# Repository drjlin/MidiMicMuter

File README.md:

# Midi Microphone Muter

This repository provides code and hardware for a little tool in the form of a Y-adapter to be used on stage to mute a single microphone by receiving a MIDI control change signal.

## Motivation

For me as a drummer doing some additional background vocals in my band, there is always the problem of cymbal bleed on the vocal microphone signal. So while I was not singing, our live mixing engineer used to turn down the volume of my microphone signal at the risk of not having it back when needed again. Since a MIDI track was already running synchronized with our show for controlling lights and guitar effects, our mixing engineer Jakob had the idea to also use the MIDI signal to mute the microphone in those parts of the songs where it is not needed. However, all available solutions were not at all compact and satisfying, so I decided to build my own device.

## How it works

The electronics pcb is designed to fit into an XLR cable connector. This way the full device is nothing more than a Y-shaped cable with two connectors on the input side (Mic and MIDI In) and one XLR connector on the output side to deliver the occasionally muted signal to the microphone preamp.

Inspired by another blog post (https://mitxela.com/projects/midi_on_the_attiny), I decided to use the 5V power line from MIDI to power an ATtiny85 which decodes the serial MIDI data and pulls outputs high for an LED and an analog switch to turn the audio off.

Contrary to the popular advice, no optocoupler was used on the receiving unit to save space and allow to directly use MIDI as a voltage source. Pros and cons of this approach are described in detail in the link above.

Another variant of the device having the electronics mounted into a separate small box is currently in the planning phase. This would allow for proper MIDI decoupling, provide an additional MIDI Out connector and XLR connectors to make it more modular and independent of the needed cable lengths. On the downside, this would take a little more space and require another voltage source (battery, 5V connector or using microphone phantom power).

## Hardware

PCB dimensions are 23.15x9.70 mm and therefore it fits nicely into a standard XLR connector. On the input side, there are pin header terminals for MIDI In (GND, +5V, Signal) and Mic In (analog GND, Signal +, Signal -). On the output side, there is an additional Mic Out 3-pin terminal. The ATtiny85 is a cheap microcontroller which can be run without any peripherals at low power, which makes it the perfect choice for processing the program logic. TS5A22364 from Texas Instruments is a 2-channel analog switch with negative signaling capability, perfectly suited for audio switching. It takes audio Signal + and Signal - on its normally closed inputs and is connected to Mic Out on its common output pins. The only additional elements on the PCB are a 33 uF capacitor for smoothing the input voltage, a pull-up resistor and a small stabilizing 1nF capacitor on the MIDI signal line, a pull-down resistor on the output line of the ATtiny85 connecting to the analog switch and an optional LED with serial resistor to visualize when the device is in mute mode (mainly for testing).

Because audio signals are connected to the normally closed pins of the analog switch, the default behavior is to let the audio flow from input to output and only mute it on respective incoming MIDI commands. But keep in mind there is no real bypass, so MIDI has to be connected (and powered) to let audio go through.

Analog (audio) GND is not connected to the digital GND by default. During tests, it was found that the two should be connected to avoid noise on the audio output, but this can easily be achieved by adding an additional cable between the respective pins.

You need to install KiCad (https://www.kicad.org) to be able to open the schematics / pcb / gerber files.

## Software

On the software side, I used a slightly modified version of Nick Gammon's MIDI decoder for ATtiny85 (https://arduino.stackexchange.com/questions/14054/interfacing-an-attiny85-with-midi-via-software-serial?answertab=active#tab-top). I just added the output switching logic when a control change command is received on the specified MIDI channel and CC number (by default: CC 63 on MIDI channel 7).

For programming the ATtiny85, Arduino IDE was used in combination with an Arduino nano as programmer. The procedure is described elsewhere in detail. I followed the description in this link: https://wolles-elektronikkiste.de/en/programming-attiny-with-arduino-code

You need to install Arduino IDE (https://www.arduino.cc/en/software) to be able use the included software.

## Usage

Connect microphone, MIDI in and microphone preamp. By default, the signal will be hearable. Sending CC 63 on MIDI channel 7 with a value between than 64 and 127 will mute the microphone and light up the LED. Another event with a value between 0 and 63 will unmute the line again.

## How to get it

Currently, I'm not planning to sell ready-to-use hardware. But I have some PCBs over that I don't need, so feel free to contact me if interested. Otherwise, everyone is invited to build the device on her / his own. Everything you need should be in the repository. If you have problems or questions, do not hesitate to ask.

## Feedback

Any feedback is appreciated, either on making the device more robust while maintaining the small footprint, or if there are any tips on implementing the in-a-box design. Also, please report any bugs in case you find some.

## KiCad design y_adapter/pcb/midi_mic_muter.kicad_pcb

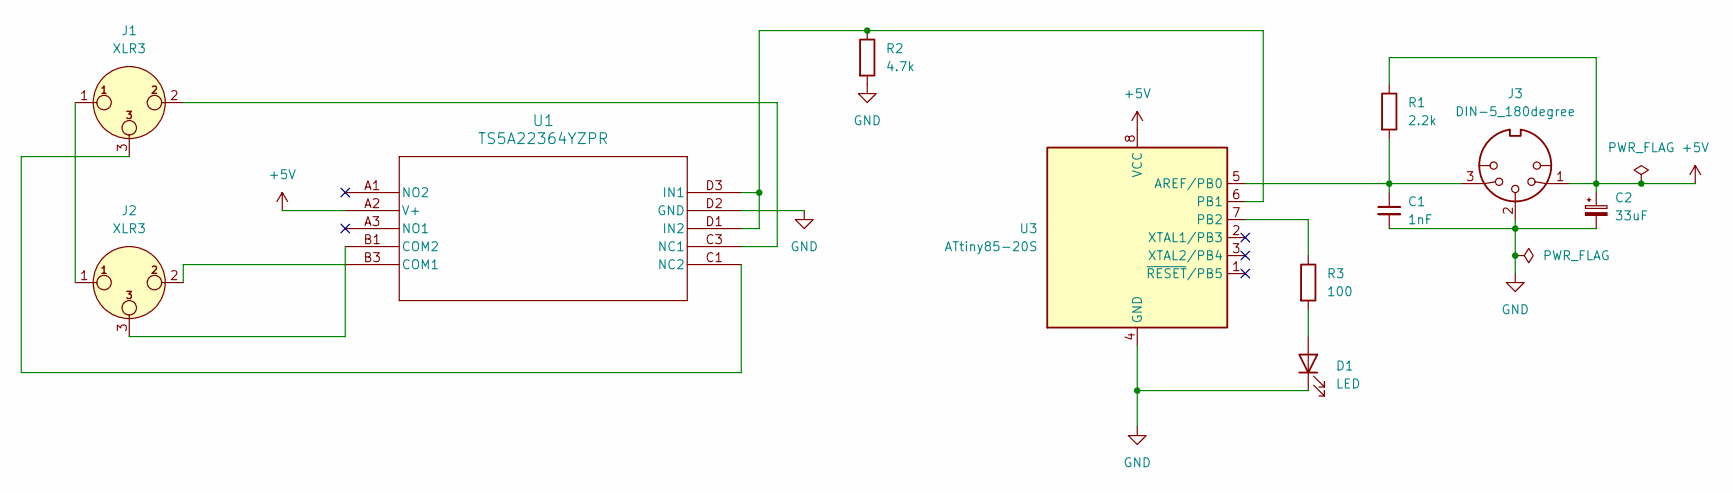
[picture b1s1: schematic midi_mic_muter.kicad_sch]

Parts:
C1: 1nF; C_0603_1608Metric
C2: 33uF; C_0805_2012Metric
D1: LED; LED_0603_1608Metric
J1, J2: XLR3; PinHeader_1x03_P2.54mm_Vertical
J3: DIN-5_180degree; PinHeader_1x03_P2.54mm_Vertical
R1: 2.2k; R_0603_1608Metric
R2: 4.7k; R_0603_1608Metric
R3: 100; R_0603_1608Metric
U1: TS5A22364YZPR; Texas_DSBGA-10_1.36x1.86mm_Layout3x4_P0.5mm
U3: ATtiny85-20S; SOIC-8W_5.3x5.3mm_P1.27mm

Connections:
+5V: C2.1, J3.1, R1.1, U1.A2 (V+), U3.8 (VCC)
GND: C1.2, C2.2, D1.1 (K), J3.2, R2.2, U1.D2 (GND), U3.4 (GND)
unnamed: D1.2 (A), R3.2
unnamed: J1.1, J2.1
unnamed: J2.2, U1.B3 (COM1)
unnamed: J2.3, U1.B1 (COM2)
unnamed: R2.1, U1.D1 (IN2), U1.D3 (IN1), U3.6 (PB1)
unnamed: J1.2, U1.C3 (NC1)
unnamed: J1.3, U1.C1 (NC2)
unnamed: C1.1, J3.3, R1.2, U3.5 (AREF/PB0)
unnamed: R3.1, U3.7 (PB2)

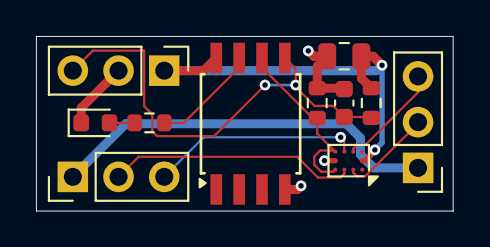
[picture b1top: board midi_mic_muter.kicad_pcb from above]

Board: 2 copper layers, 23.1 x 9.7 mm, 11 parts (0 on the bottom side), 11 nets.

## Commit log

2024-07-20 initialized repo
2024-07-20 added license
